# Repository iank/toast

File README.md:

PAC1953T-E/J6CX power monitor
	16-WLCSP, 3-channel, high side

MCP2221A I2C-USB bridge

Update fields:

```
kifield --extract toast.kicad_sch --recurse --group --norange --insert toast.csv
kifield -x toast.csv -i toast.kicad_sch -w -r
```

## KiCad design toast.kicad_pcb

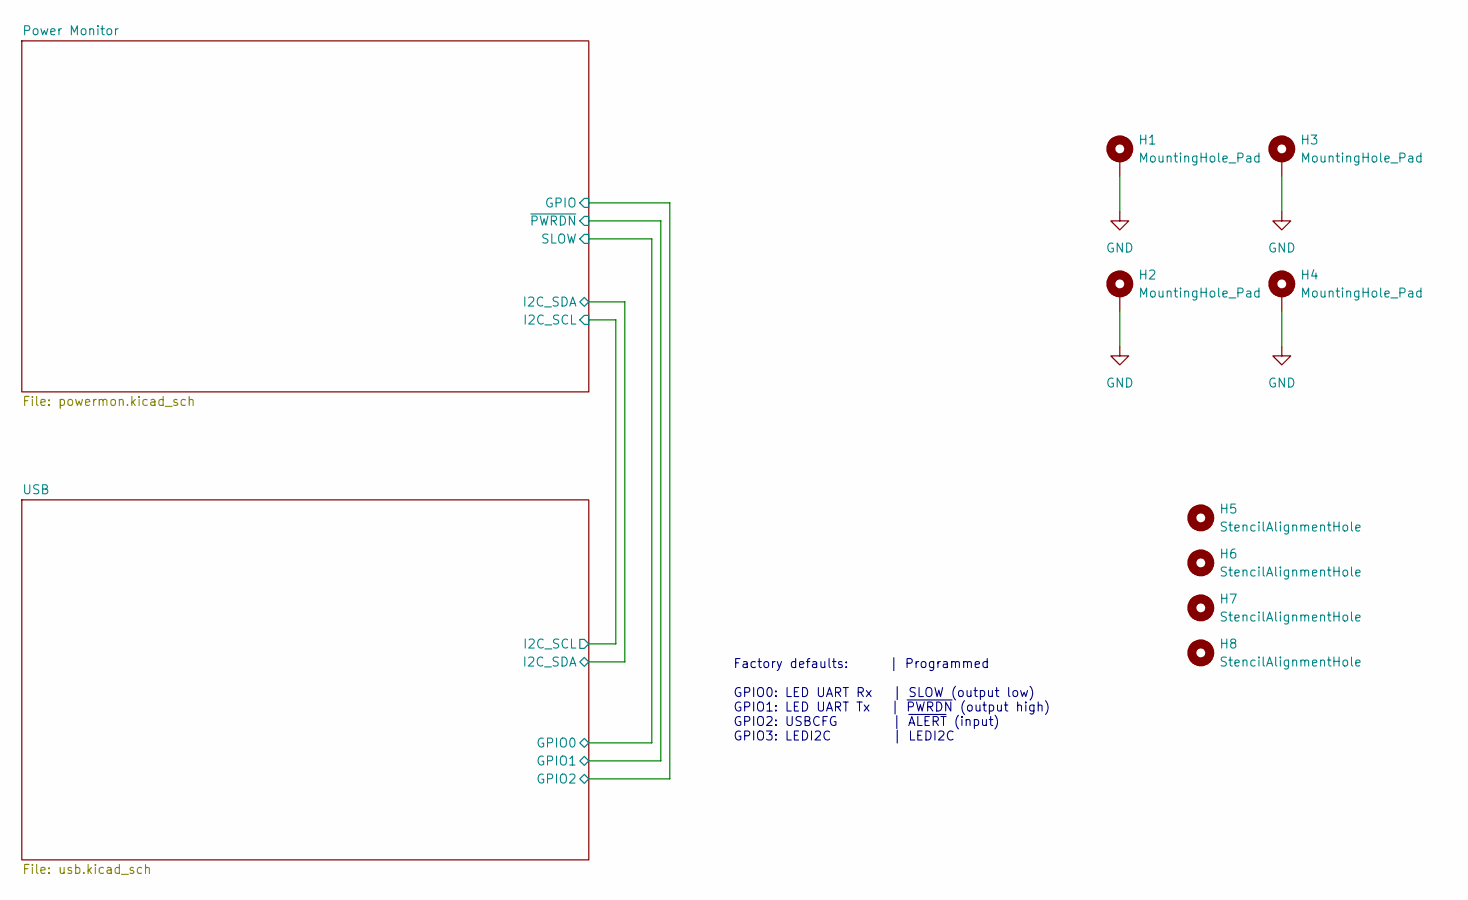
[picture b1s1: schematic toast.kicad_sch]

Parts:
H1, H2, H3, H4: MountingHole_Pad; MountingHole_2.2mm_M2_Pad
H5, H6, H7, H8: StencilAlignmentHole; StencilAlignmentHole_1.6mm

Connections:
GND: H1.1, H2.1, H3.1, H4.1; also elsewhere on the board

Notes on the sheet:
Factory defaults: | Programmed GPIO0: LED UART Rx | SLOW (output low) GPIO1: LED UART Tx | ~{PWRDN} (output high) GPIO2: USBCFG | ~{ALERT} (input) GPIO3: LEDI2C | LEDI2C

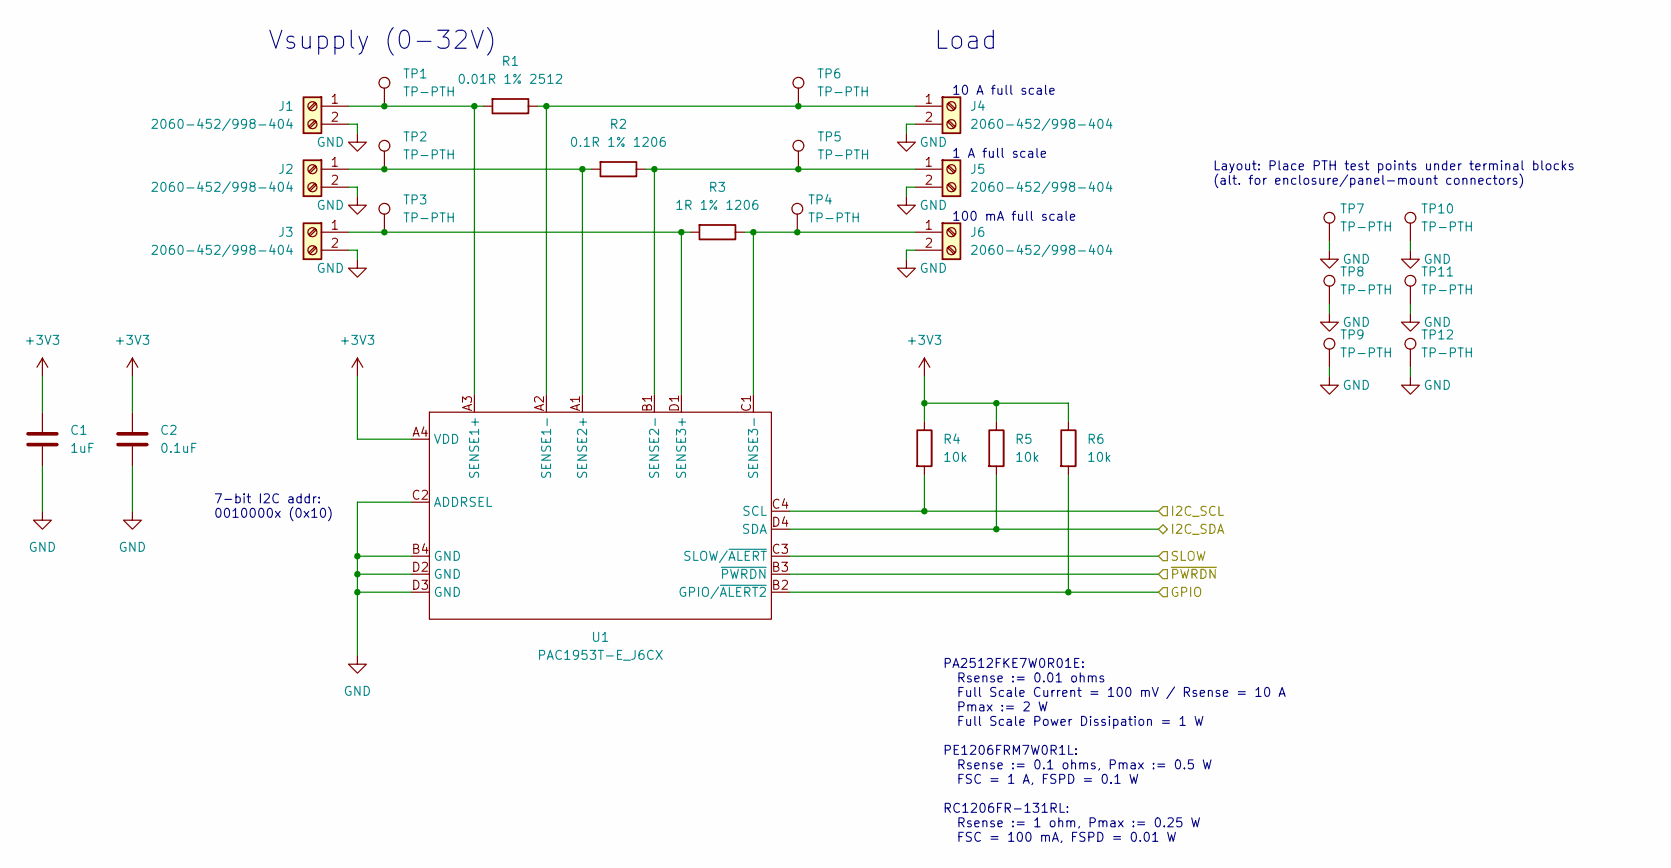
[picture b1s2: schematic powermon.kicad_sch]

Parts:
C1: 1uF; C_0603_1608Metric; MfgPartNo GENERIC
C2: 0.1uF; C_0402_1005Metric; MfgPartNo GENERIC
J1, J2, J3, J4, J5, J6: 2060-452/998-404; WAGO_2060-452_998-404; MfgPartNo 2060-452/998-404
R1: 0.01R 1% 2512; R_2512_6332Metric; MfgPartNo PA2512FKE7W0R01E
R2: 0.1R 1% 1206; R_1206_3216Metric; MfgPartNo PE1206FRM7W0R1L
R3: 1R 1% 1206; R_1206_3216Metric; MfgPartNo RC1206FR-131RL
R4, R5, R6: 10k; R_0402_1005Metric; MfgPartNo GENERIC
TP1, TP2, TP3, TP4, TP5, TP6, TP7, TP8, TP9, TP10, TP11, TP12: TP-PTH; TestPoint_THTPad_D4.0mm_Drill2.0mm
U1: PAC1953T-E_J6CX; BGA16NP50_4X4_222X217X67B32N; MfgPartNo PAC1953T-E/J6CX

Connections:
+3V3: C1.1, C2.1, R4.1, R5.1, R6.1, U1.A4 (VDD); also elsewhere on the board
/Power Monitor/GPIO: R6.2, U1.B2 (GPIO/~ALERT2); also elsewhere on the board
/Power Monitor/I2C_SCL: R4.2, U1.C4 (SCL); also elsewhere on the board
/Power Monitor/I2C_SDA: R5.2, U1.D4 (SDA); also elsewhere on the board
/Power Monitor/SLOW: U1.C3 (SLOW/~ALERT); also elsewhere on the board
/Power Monitor/~PWRDN: U1.B3 (~PWRDN); also elsewhere on the board
GND: C1.2, C2.2, J1.2, J1.4, J2.2, J2.4, J3.2, J3.4, J4.2, J4.4, J5.2, J5.4, J6.2, J6.4, TP7.1, TP8.1, TP9.1, TP10.1, TP11.1, TP12.1, U1.B4 (GND), U1.C2 (ADDRSEL), U1.D2 (GND), U1.D3 (GND); also elsewhere on the board
unnamed: J1.1, J1.3, R1.2, TP1.1, U1.A3 (SENSE1+)
unnamed: J2.1, J2.3, R2.2, TP2.1, U1.A1 (SENSE2+)
unnamed: J3.1, J3.3, R3.2, TP3.1, U1.D1 (SENSE3+)
unnamed: J4.1, J4.3, R1.1, TP6.1, U1.A2 (SENSE1-)
unnamed: J5.1, J5.3, R2.1, TP5.1, U1.B1 (SENSE2-)
unnamed: J6.1, J6.3, R3.1, TP4.1, U1.C1 (SENSE3-)

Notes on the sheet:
Load
100 mA full scale
Layout: Place PTH test points under terminal blocks (alt. for enclosure/panel-mount connectors)
7-bit I2C addr: 0010000x (0x10)
10 A full scale
1 A full scale
PA2512FKE7W0R01E: Rsense := 0.01 ohms Full Scale Current = 100 mV / Rsense = 10 A Pmax := 2 W Full Scale Power Dissipation = 1 W PE1206FRM7W0R1L: Rsense := 0.1 ohms, Pmax := 0.5 W FSC = 1 A, FSPD = 0.1 W RC1206FR-131RL: Rsense := 1 ohm, Pmax := 0.25 W FSC = 100 mA, FSPD = 0.01 W
Vsupply (0-32V)

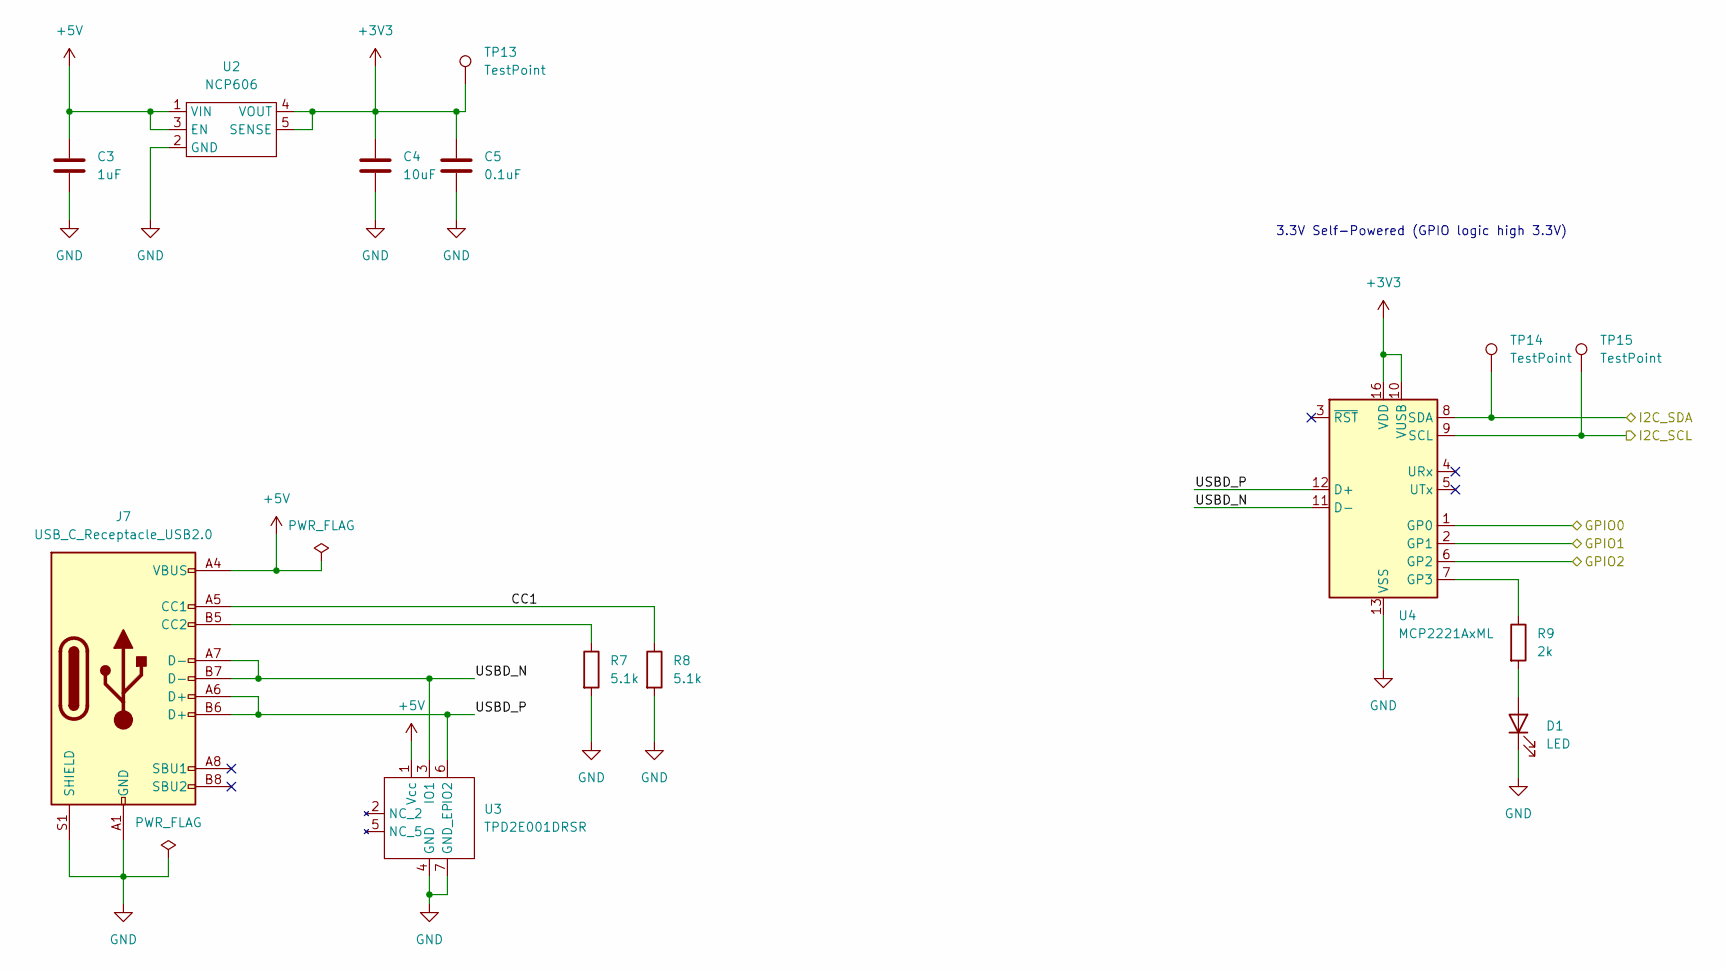
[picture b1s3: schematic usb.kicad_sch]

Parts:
C3: 1uF; C_0603_1608Metric; MfgPartNo GENERIC
C4: 10uF; C_0805_2012Metric; MfgPartNo GENERIC
C5: 0.1uF; C_0402_1005Metric; MfgPartNo GENERIC
D1: LED; LED_0603_1608Metric; MfgPartNo 150060VS55040
J7: USB_C_Receptacle_USB2.0; USB_C_Receptacle_GCT_USB4085; MfgPartNo USB4085-GF-A
R7, R8: 5.1k; R_0402_1005Metric; MfgPartNo GENERIC
R9: 2k; R_0402_1005Metric; MfgPartNo GENERIC
TP13, TP14, TP15: TestPoint; TestPoint_Pad_D2.0mm
U2: NCP606; SON7P95_300X330X100L50X35T200X120N; MfgPartNo NCP606MN33T2G
U3: TPD2E001DRSR; SON7P95_300X300X80L50X35T190X120N; MfgPartNo TPD2E001DRSR
U4: MCP2221AxML; QFN-16-1EP_4x4mm_P0.65mm_EP2.5x2.5mm; MfgPartNo MCP2221A-I/ML

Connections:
+3V3: C4.1, C5.1, TP13.1, U2.4 (VOUT), U2.5 (SENSE), U4.10 (VUSB), U4.16 (VDD); also elsewhere on the board
+5V: C3.1, J7.A4 (VBUS), J7.A9 (VBUS), J7.B4 (VBUS), J7.B9 (VBUS), U2.1 (VIN), U2.3 (EN), U2.6 (VIN), U3.1 (Vcc)
/Power Monitor/GPIO: U4.6 (GP2); also elsewhere on the board
/Power Monitor/I2C_SCL: TP15.1, U4.9 (SCL); also elsewhere on the board
/Power Monitor/I2C_SDA: TP14.1, U4.8 (SDA); also elsewhere on the board
/Power Monitor/SLOW: U4.1 (GP0); also elsewhere on the board
/Power Monitor/~PWRDN: U4.2 (GP1); also elsewhere on the board
/USB/CC1: J7.A5 (CC1), R8.1
/USB/USBD_N: J7.A7 (D-), J7.B7 (D-), U3.3 (IO1), U4.11 (D-)
/USB/USBD_P: J7.A6 (D+), J7.B6 (D+), U3.6 (IO2), U4.12 (D+)
GND: C3.2, C4.2, C5.2, D1.1 (K), J7.A1 (GND), J7.A12 (GND), J7.B1 (GND), J7.B12 (GND), J7.S1 (SHIELD), R7.2, R8.2, U2.2 (GND), U2.7 (GND), U3.4 (GND), U3.7 (GND_EP), U4.13 (VSS); also elsewhere on the board
unnamed: D1.2 (A), R9.2
unnamed: J7.B5 (CC2), R7.1
unnamed: R9.1, U4.7 (GP3)

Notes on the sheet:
3.3V Self-Powered (GPIO logic high 3.3V)

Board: 2 copper layers, 49 parts (0 on the bottom side), 20 nets, no tracks yet.

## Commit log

2022-05-02 Kicad gitignore
2022-05-03 WiP: Added USB-I2C bridge
2022-05-04 WiP: PAC1953 power monitor
2022-05-04 WiP: PAC1953 addrsel
2022-05-04 PAC1953 shunt resistors, terminals
2022-05-05 Associate built-in footprints
2022-05-05 Add part number fields in schematic
2022-05-14 Add stencil alignment holes
2022-05-15 Project symbol library
2022-05-15 Associate LED footprint; create/associate TVS diode footprint
2022-05-15 NCP606 footprint
2022-05-15 PAC1953 footprint
2022-05-15 Stencil alignment holes and WAGO 2060-452 footprint
2022-05-15 Tweak PAC1953 and WAGO 2060 footprints

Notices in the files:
parts and their libraries:
Copyright 2021 Accelerated Designs. All rights reserved.
